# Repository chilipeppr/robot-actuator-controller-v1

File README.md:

# robot-actuator-controller-v1
This is a controller for the WE-R2.4 robot on Thingiverse.

It has an ESP32 at the heart of the controller to enable control of the actuator via Wifi or Bluetooth. There is a DC to DC converter to step down the 24v driving the DRV8825 stepper motor driver to 5V for powering the ESP32. The DRV8825 has all ports connected into the ESP32 to send step and direction pulses for control of the stepper motor.

There is also a WS2812 LED connected for indicating status of the controller.

A switch has been added for when you're using the USB port for programming the ESP32. You need to switch off the 5V from the DC to DC converter to connect USB from your computer.

The wrist cap has been extended from Jeff Kerr's original design to fit this larger board.

# Eagle Board and Schematic

The .brd and .sch files are Eagle board and schematic files. You can download Eagle for free to view or edit the boards or just use the .zip file in the "pcb fabricator" folder to send to your board house like JLCPCB where it only costs $2 to get your boards made.

# ESP32 Firmware

You need to upload the firmware in this repo to your ESP32 using esptool.py which is available on the Espressif website. There's also a video on http://chilipeppr.com/esp32 on how to use the workspace. This video shows you how to upload the firmware and use the workspace to upload code.

To program your board with this firmware use the command on Windows:
esptool.py --port COM5 write_flash 0x1000 bootloader.bin 0x10000 NodeMCU.bin 0x8000 partitions.bin

You need to install esptool.py via Python's package manager or from downloading direct from Espressif's website.

An alternate path is to use the esp32tool.zip I provide in the workspace and swap out the NodeMCU.bin file in this repo to the one in that zip file. Then install. You do need 3 .bin files to program the firmware. 2 of them are standard (bootloader.bina nd partitions.bin), but the NodeMCU.bin is the new file you'd have to swap in.

This firmware is configured for 230,400 baud, so don't forget to change to that value in ChiliPeppr when you connect to the board. If you try the default 115,200 it will fail.

# CAD Design Fusion 360

The CAD design of the extended wrist cap with the electronics inside is available at https://gallery.autodesk.com/fusion360/projects/robot-arm-esp32-drv8825-actuator-controller

# How to Upload the Lua Code

The ChiliPeppr ESP32 for Lua Workspace was used to program the board and is available at http://chilipeppr.com/esp32

Video on how to use the ESP32 for Lua workspace to upload firmware and Lua code on your ESP32. https://www.youtube.com/watch?v=njAeHfoVIoY

# Thingiverse

Jeff Kerr's (LoboCNC) original 3D printed robot arm design is on Thingiverse at https://www.thingiverse.com/thing:3327968/

# PCB Components

ESP32 Wemos $8 (Many ESP32 devices are cheaper, but this is the smallest size broadly available to fit inside the small actuators)
https://www.aliexpress.com/item/ESP32-wemos-ESP32-WiFi-Modules-Bluetooth-Dual-ESP-32-ESP-32S-ESP8266/32815190965.html

DRV8825 Stepper Board $0.95
https://www.aliexpress.com/item/5pcs-lot-3D-Printer-Stepstick-Drv8825-Stepper-Motor-Driver-Reprap-4-PCB-Board-Free-shipping-replace/32514641632.html

DC to DC Converter $0.90 (Pick the 5V version, not 3.3V)
https://www.aliexpress.com/item/DC-DC-Power-Supply-Module-Step-Down-3A-output-24V-12V-to-5V-3-3V-Buck/32904709711.html

WS2812B LED $0.15 per (Choose white and WS2812B)
https://www.aliexpress.com/item/10-1000pcs-4-Pin-WS2812B-WS2812-LED-Chip-Heatsink-5V-5050-RGB-WS2811-IC-Built-in/32634454437.html

Slide Switch $0.29 for 20 pieces
https://www.aliexpress.com/item/20Pcs-Interruptor-on-off-mini-Slide-Switch-SS12D00-SS12D00G3-3pin-1P2T-2-Position-High-quality-toggle/32964400942.html

Screw Terminal
https://www.aliexpress.com/item/20-pcs-2-Pin-Screw-blue-green-PCB-Terminal-Block-Connector-5mm-Pitch/32814618602.html

26AWG Silicone Ultra Flexible Wire for 24v (Use 2 of the 4 wires)
https://www.aliexpress.com/item/2metre-26AWG-28AWG-30AWG-Silicone-Wire-Ultra-Flexiable-Test-Line-3P-4P-6P-0-08mm-Tinned/32870367030.html

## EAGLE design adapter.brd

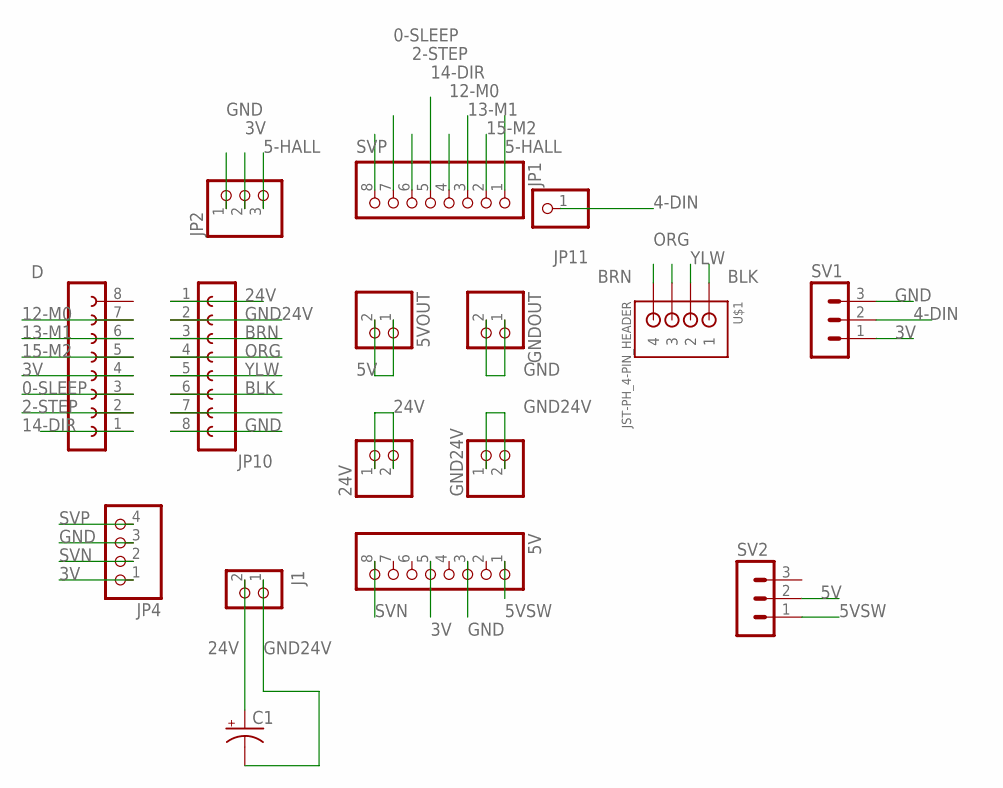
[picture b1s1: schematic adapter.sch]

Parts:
5V: PINHD-1X8; 1X08
5VOUT, 24V: PINHD-1X2; 1X02
C1: CPOL-USE5-6; E5-6
D: FE08-1; FE08
GND24V: PINHD-1X2; 1X02
GNDOUT: PINHD-1X2; 1X02
J1: CON_TERMINAL_BLOCK_02-5MM; TERMINAL_BLOCK_2P_5
JP1: PINHD-1X8; 1X08
JP2: PINHD-1X3; 1X03
JP4: PINHD-1X4; 1X04
JP10: FE08-1; FE08
JP11: PINHD-1X1; 1X01
SV1, SV2: MA03-1
U$1: JST-PH_4-PIN_HEADER; JST_B4B-PH_HEADER

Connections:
0-SLEEP: D.3, JP1.7
2-STEP: D.2, JP1.6
3V: 5V.5, D.4, JP2.2, JP4.1, SV1.1
4-DIN: JP11.1, SV1.2
5-HALL: JP1.1, JP2.3
5V: 5VOUT.1, 5VOUT.2, SV2.2
5VSW: 5V.1, SV2.1
12-M0: D.7, JP1.4
13-M1: D.6, JP1.3
14-DIR: D.1, JP1.5
15-M2: D.5, JP1.2
24V: 24V.1, 24V.2, C1.+, J1.2, JP10.1
BLK: JP10.6, U$1.P1 (1)
BRN: JP10.3, U$1.P4 (4)
GND: 5V.3, GNDOUT.1, GNDOUT.2, JP2.1, JP4.3, JP10.8, SV1.3
GND24V: C1.-, GND24V.1, GND24V.2, J1.1, JP10.2
ORG: JP10.4, U$1.P3 (3)
SVN: 5V.8, JP4.2
SVP: JP1.8, JP4.4
YLW: JP10.5, U$1.P2 (2)

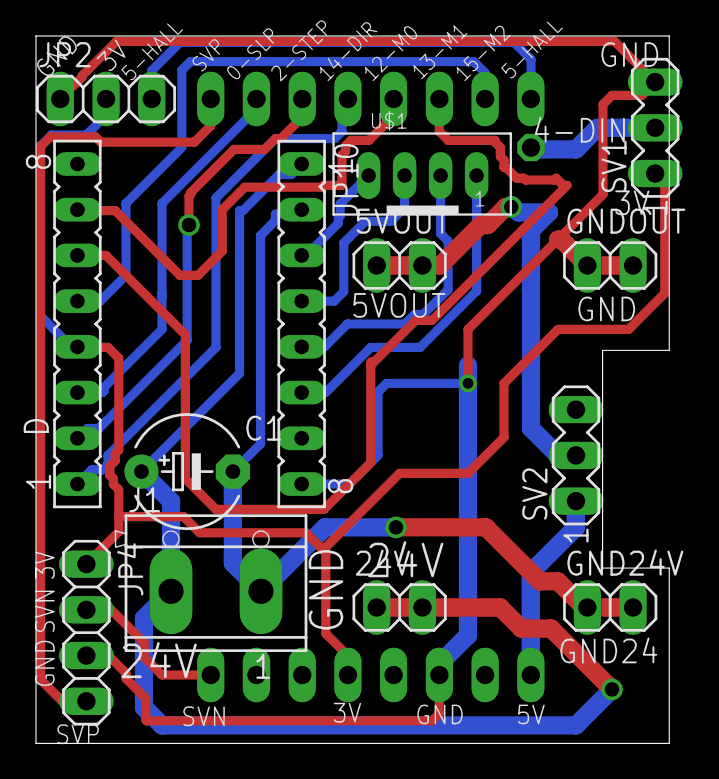
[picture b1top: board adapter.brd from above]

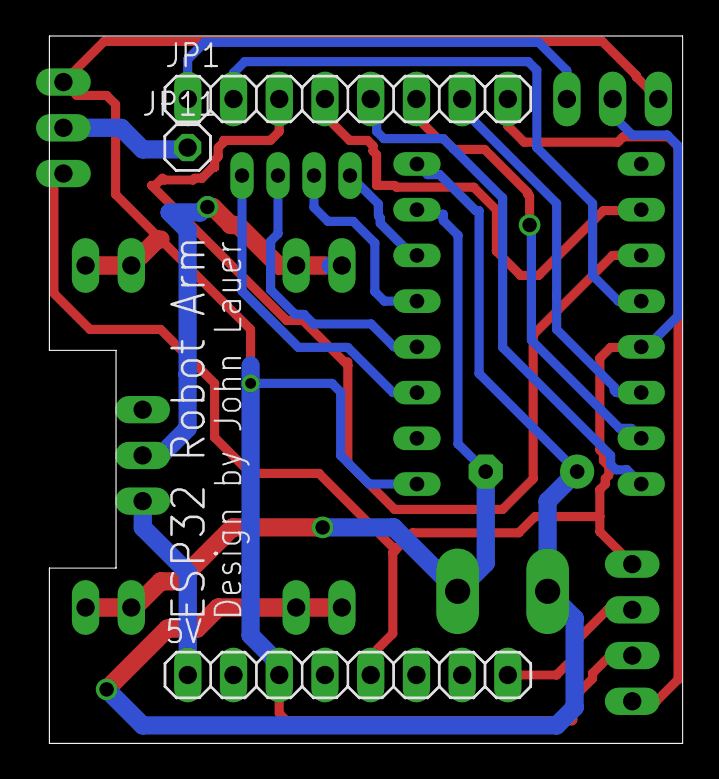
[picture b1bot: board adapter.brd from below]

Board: 2 copper layers, 35.2 x 39.3 mm, 16 parts (3 on the bottom side), 20 nets.

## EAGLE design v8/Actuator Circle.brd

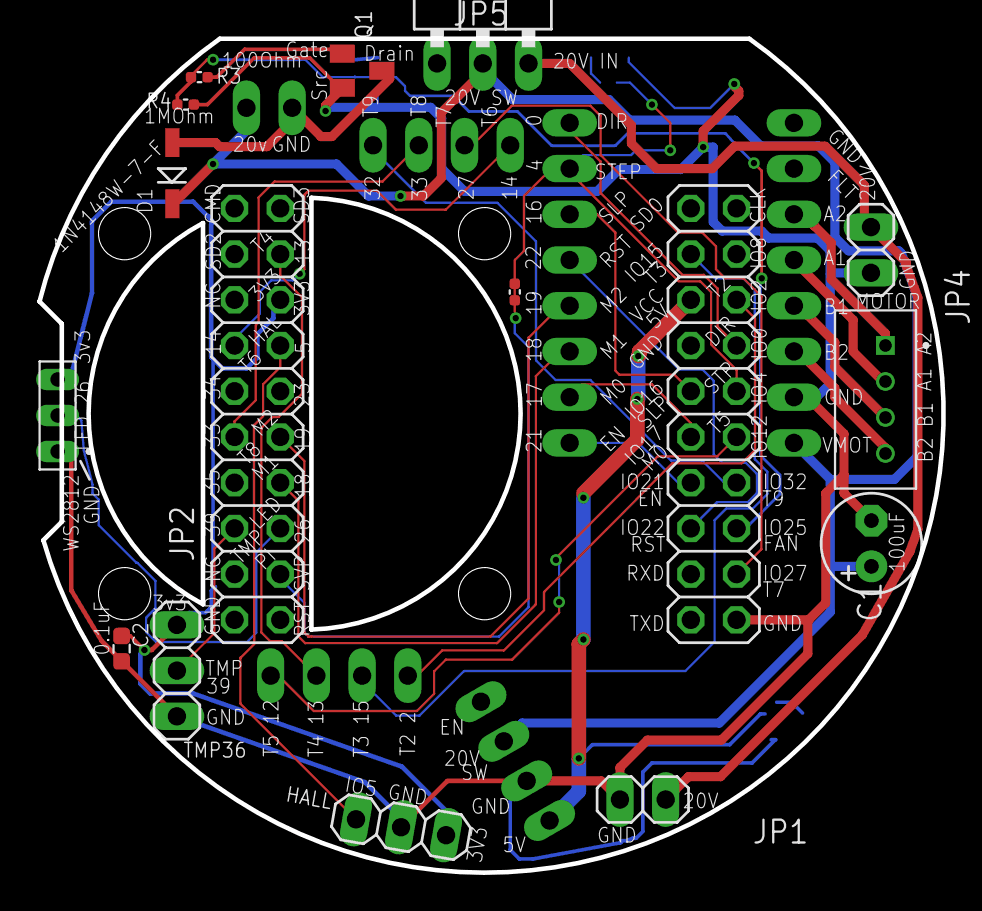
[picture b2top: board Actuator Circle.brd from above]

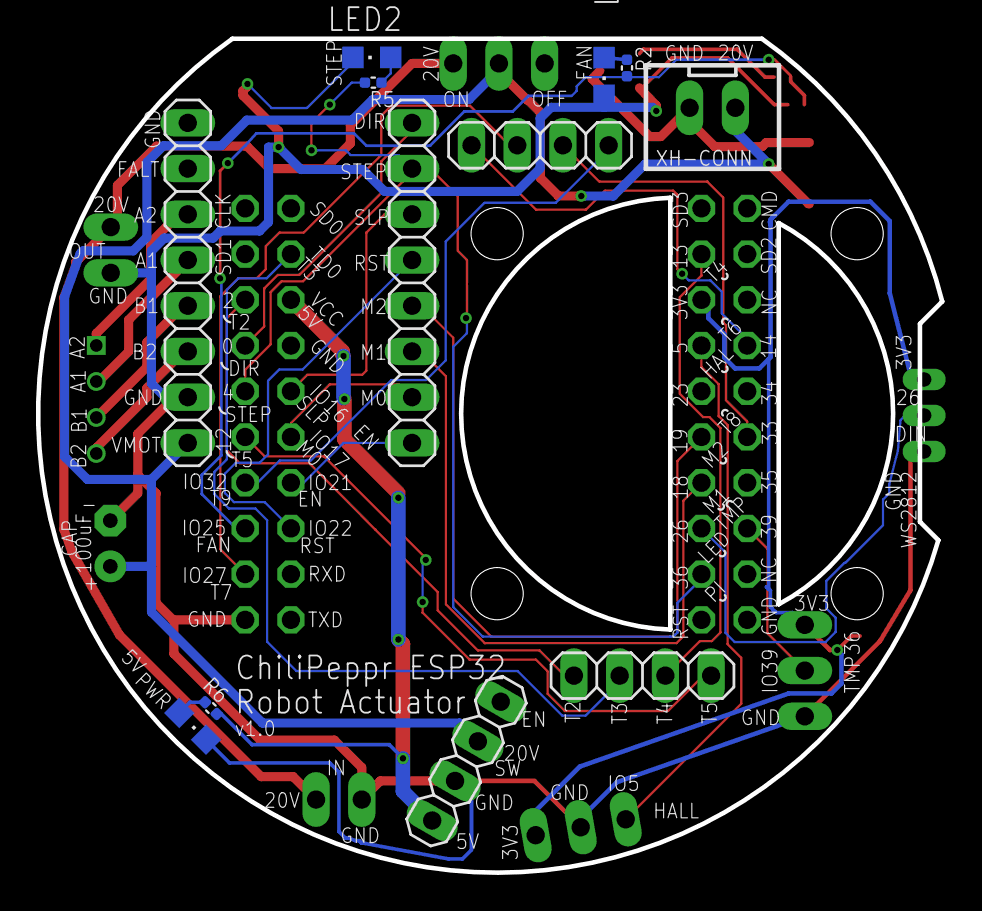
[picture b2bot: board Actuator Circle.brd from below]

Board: 2 copper layers, 50.2 x 46.3 mm, 28 parts (12 on the bottom side), 36 nets.

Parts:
5V: 17-21SURC/S530-A3/TR8; CHIPLED_0805
C1: 100UF; E2,5-6
C2: 0.1uf; CAP_0603
D1: 1N4148W-7-F; SOD123
HALL: 1X03
JP1, JP4: 1X02
JP2, JP3: 2X10
JP5: 1X03/90
JP8, JP9: 1X08
JP10, JP11, JP12: 1X04
LED1, LED2: 17-21SURC/S530-A3/TR8; CHIPLED_0805
MOTOR: B4B-PH-K-S(LF)(SN); JST_B4B-PH-K-S(LF)(SN)
Q1: FDV301N; SOT23
R1: 0 Ohm; RES_0402
R2, R5: 1K; RES_0402
R3: 100Ohm; RES_0402
R4: 1MOhm; RES_0402
R6: 2k; RES_0402
TMP36: 1X03
WS2812: PIN1X3-2MM
XH-CONN: JST-XH-02-PIN-LONG-PAD; JST-XH-02-PACKAGE-LONG-PAD

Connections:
3V3: C2.1, HALL.1, JP2.15, TMP36.3, WS2812.3
5V: JP3.16, JP12.1, R6.2
20V: JP1.2, JP4.2, JP5.3
20V-SW: C1.+, D1.1, JP5.2, JP9.1, JP12.3, XH-CONN.1
A1: JP9.5, MOTOR.2
A2: JP9.6, MOTOR.1
B1: JP9.4, MOTOR.3
B2: JP9.3, MOTOR.4
DIR-IO0: JP3.13, JP8.8
DRAIN: D1.2, Q1.3, XH-CONN.2
EN-IO21: JP3.8, JP8.1
FAN-GATE: Q1.1, R3.1
FAN-IO25: JP3.5, R2.2, R3.2, R4.2
GND: 5V.C, C1.-, C2.2, HALL.2, JP1.1, JP2.2, JP3.1, JP3.14, JP4.1, JP9.2, JP9.8, JP12.2, LED1.C, LED2.C, Q1.2, R4.1, TMP36.1, WS2812.1
HALL-IO5: HALL.3, JP2.13
LED-IO26: JP2.5, WS2812.2
M0-IO17: JP3.10, JP8.2
M1-IO18: JP2.7, JP8.3
M2-IO19: JP2.9, JP8.4
unnamed: LED1.A, R2.1
unnamed: LED2.A, R5.1
unnamed: 5V.A, R6.1
NC: JP2.4, JP2.16
PI-IO36: JP2.3, R1.2
RST-IO22: JP3.6, JP8.5
SLP-IO16: JP3.12, JP8.6
STEP-IO4: JP3.11, JP8.7, R1.1, R5.2
T2-IO2: JP3.15, JP10.1
T3-IO15: JP3.18, JP10.2
T4-IO13: JP2.17, JP10.3
T5-IO12: JP3.9, JP10.4
T6-IO14: JP2.14, JP11.1
T7-IO27: JP3.3, JP11.2
T8-IO33: JP2.10, JP11.3
T9-IO32: JP3.7, JP11.4
TMP-IO39: JP2.6, TMP36.2

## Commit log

2019-03-05 Initial check in of firmware and Lua code
2019-03-05 Send this zip to board fabricator
2019-03-22 Fixed the correct PCB
2019-08-19 v8 update
